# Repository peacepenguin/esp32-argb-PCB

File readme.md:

Kicad PCB for creating a simple ESP32 based open source 8-channel ARGB controller for PC 5v ARGB devices, or any other WS2812 5v LED strips.

Works well paired with "WLED" esp32 software. Using "multi-pin" fork found here:
https://github.com/peacepenguin/WLED

WLED works with "OpenRGB" via serial too. So you can integrate this hardware design into a system controlled by OpenRGB via the "TPM2" serial protocol.

Hardware footprint based on 30-pin "Devkit v1" (15 pins on each side):
https://www.aliexpress.com/item/1005001648850998.html

Also expects 74HCT245N 8-channel level shifter, and 8x JST-XH angle headers.

ESP32 footprint used in Kicad is by Victor Lamoine, licensed BSD-3-Clause-Attribution License
'This product includes software developed by Victor Lamoine.'

74HCT245N footprint by SnapEDA:

#(c) SnapEDA 2016 (snapeda.com)
#This work is licensed under a Creative Commons Attribution-ShareAlike 4.0 International License (CC BY-SA) with Design Exception 1.0
#

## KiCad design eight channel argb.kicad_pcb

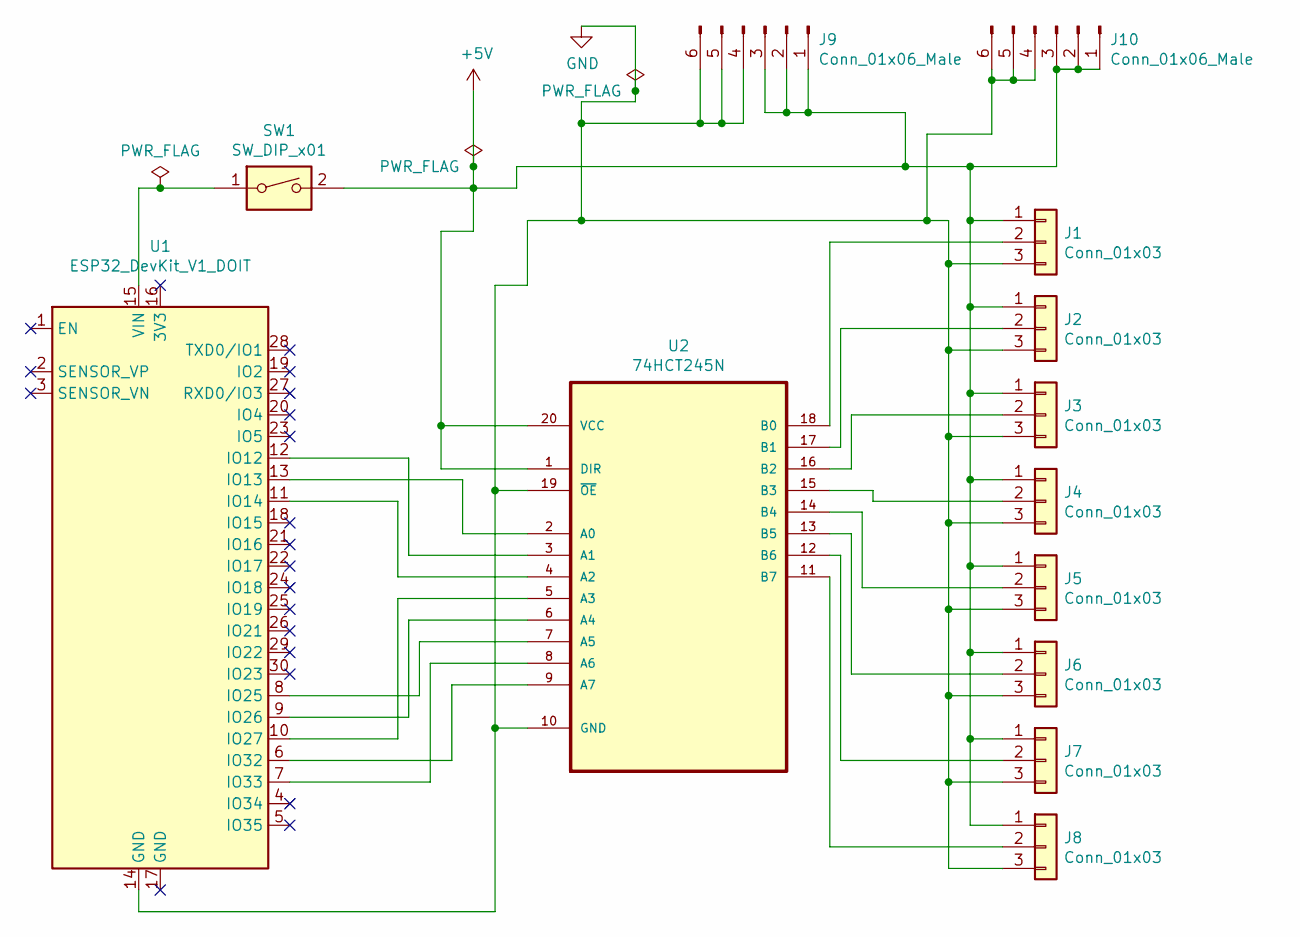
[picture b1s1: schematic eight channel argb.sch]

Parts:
J1, J2, J3, J4, J5, J6, J7, J8: Conn_01x03; JST_XH_S3B-XH-A_1x03_P2.50mm_Horizontal
J9, J10: Conn_01x06_Male; JST_XH_S6B-XH-A_1x06_P2.50mm_Horizontal
SW1: SW_DIP_x01; SW_DIP_SPSTx01_Slide_6.7x4.1mm_W7.62mm_P2.54mm_LowProfile
U1: ESP32_DevKit_V1_DOIT; esp32_devkit_v1_doit
U2: 74HCT245N; DIP254P762X420-20; MPN 74HCT245N

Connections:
+5V: J1.1, J2.1, J3.1, J4.1, J5.1, J6.1, J7.1, J8.1, J9.1, J9.2, J9.3, J10.1, J10.2, J10.3, SW1.2, U2.1 (DIR), U2.20 (VCC)
GND: J1.3, J2.3, J3.3, J4.3, J5.3, J6.3, J7.3, J8.3, J9.4, J9.5, J9.6, J10.4, J10.5, J10.6, U1.14 (GND), U2.10 (GND), U2.19 (~OE)
unnamed: J1.2, U2.18 (B0)
unnamed: J2.2, U2.17 (B1)
unnamed: J3.2, U2.16 (B2)
unnamed: J4.2, U2.15 (B3)
unnamed: J5.2, U2.14 (B4)
unnamed: J6.2, U2.13 (B5)
unnamed: J7.2, U2.12 (B6)
unnamed: J8.2, U2.11 (B7)
unnamed: SW1.1, U1.15 (VIN)
unnamed: U1.6 (IO32), U2.9 (A7)
unnamed: U1.7 (IO33), U2.8 (A6)
unnamed: U1.8 (IO25), U2.7 (A5)
unnamed: U1.9 (IO26), U2.6 (A4)
unnamed: U1.10 (IO27), U2.5 (A3)
unnamed: U1.11 (IO14), U2.4 (A2)
unnamed: U1.12 (IO12), U2.3 (A1)
unnamed: U1.13 (IO13), U2.2 (A0)

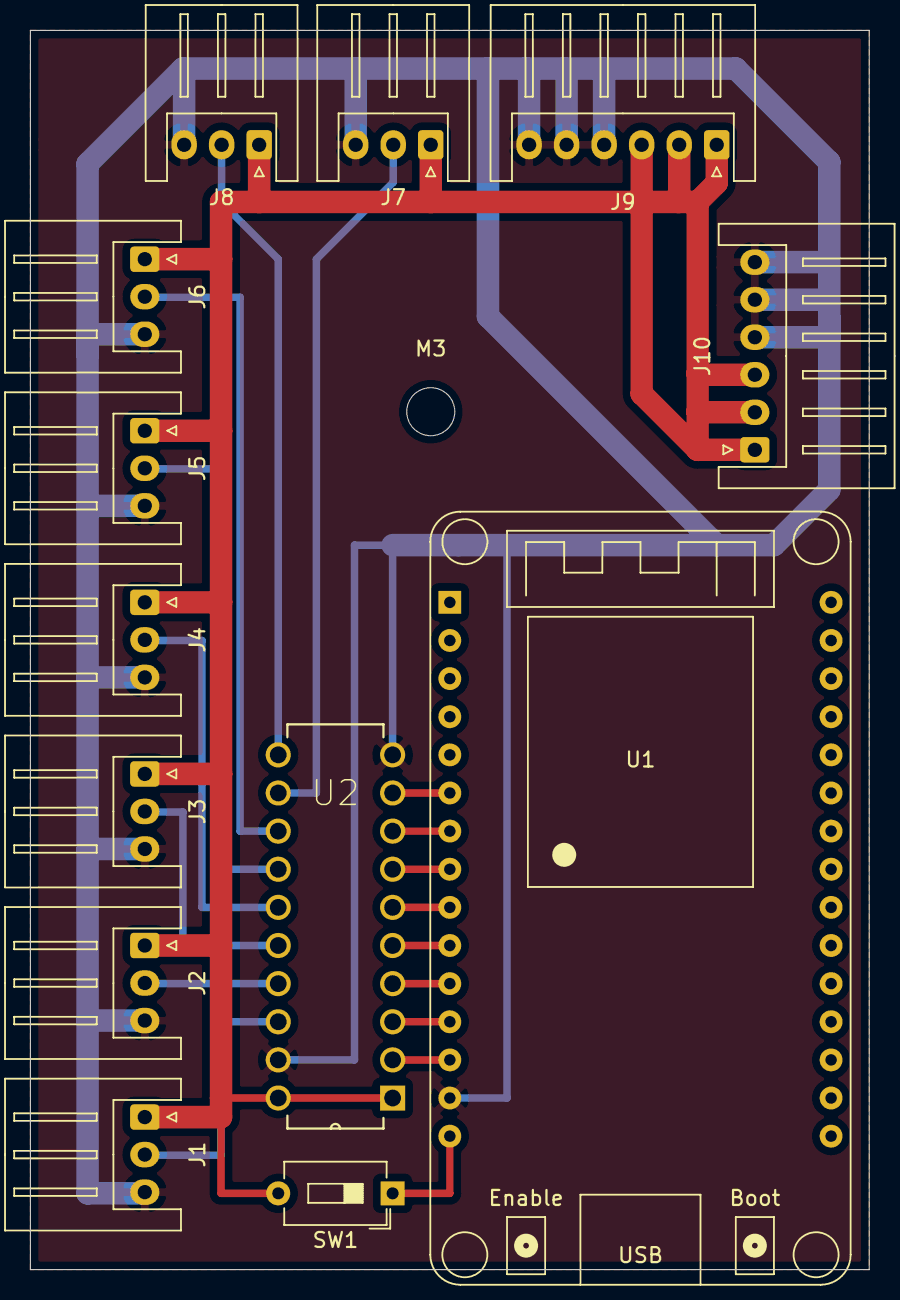
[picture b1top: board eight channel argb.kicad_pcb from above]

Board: 2 copper layers, 55.9 x 82.6 mm, 14 parts (0 on the bottom side), 19 nets.

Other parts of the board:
M3: MountingHole_3.2mm_M3
